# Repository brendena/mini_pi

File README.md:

# MINI_PI

The goal is to make a board that you can use to replace the inside of a mac mini.  

The goal is to use as much of the original as possible.  
* case
* power supply
* wifi antenna 
* heatsink
* fan

Parts
* Mac mini 2013

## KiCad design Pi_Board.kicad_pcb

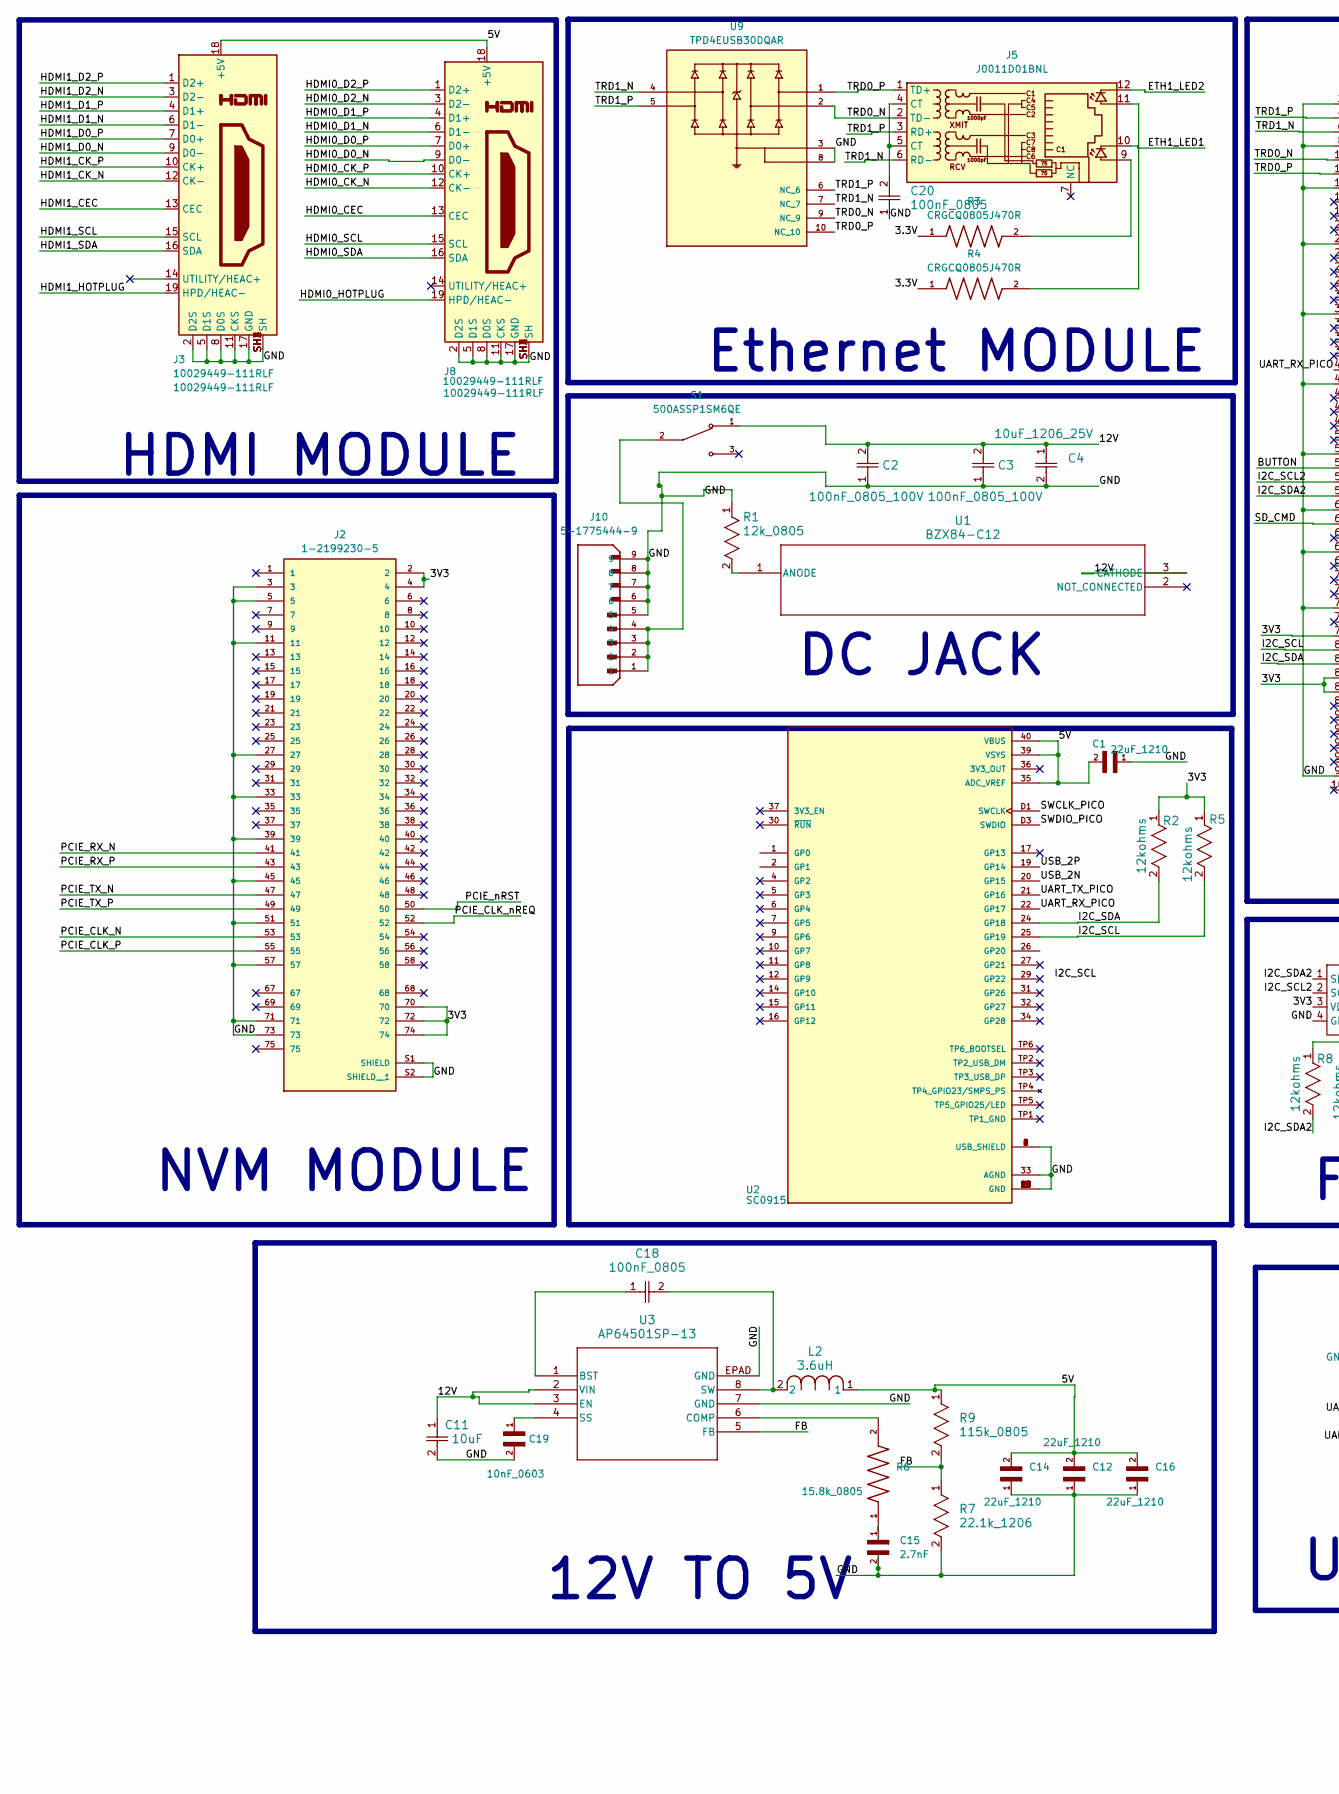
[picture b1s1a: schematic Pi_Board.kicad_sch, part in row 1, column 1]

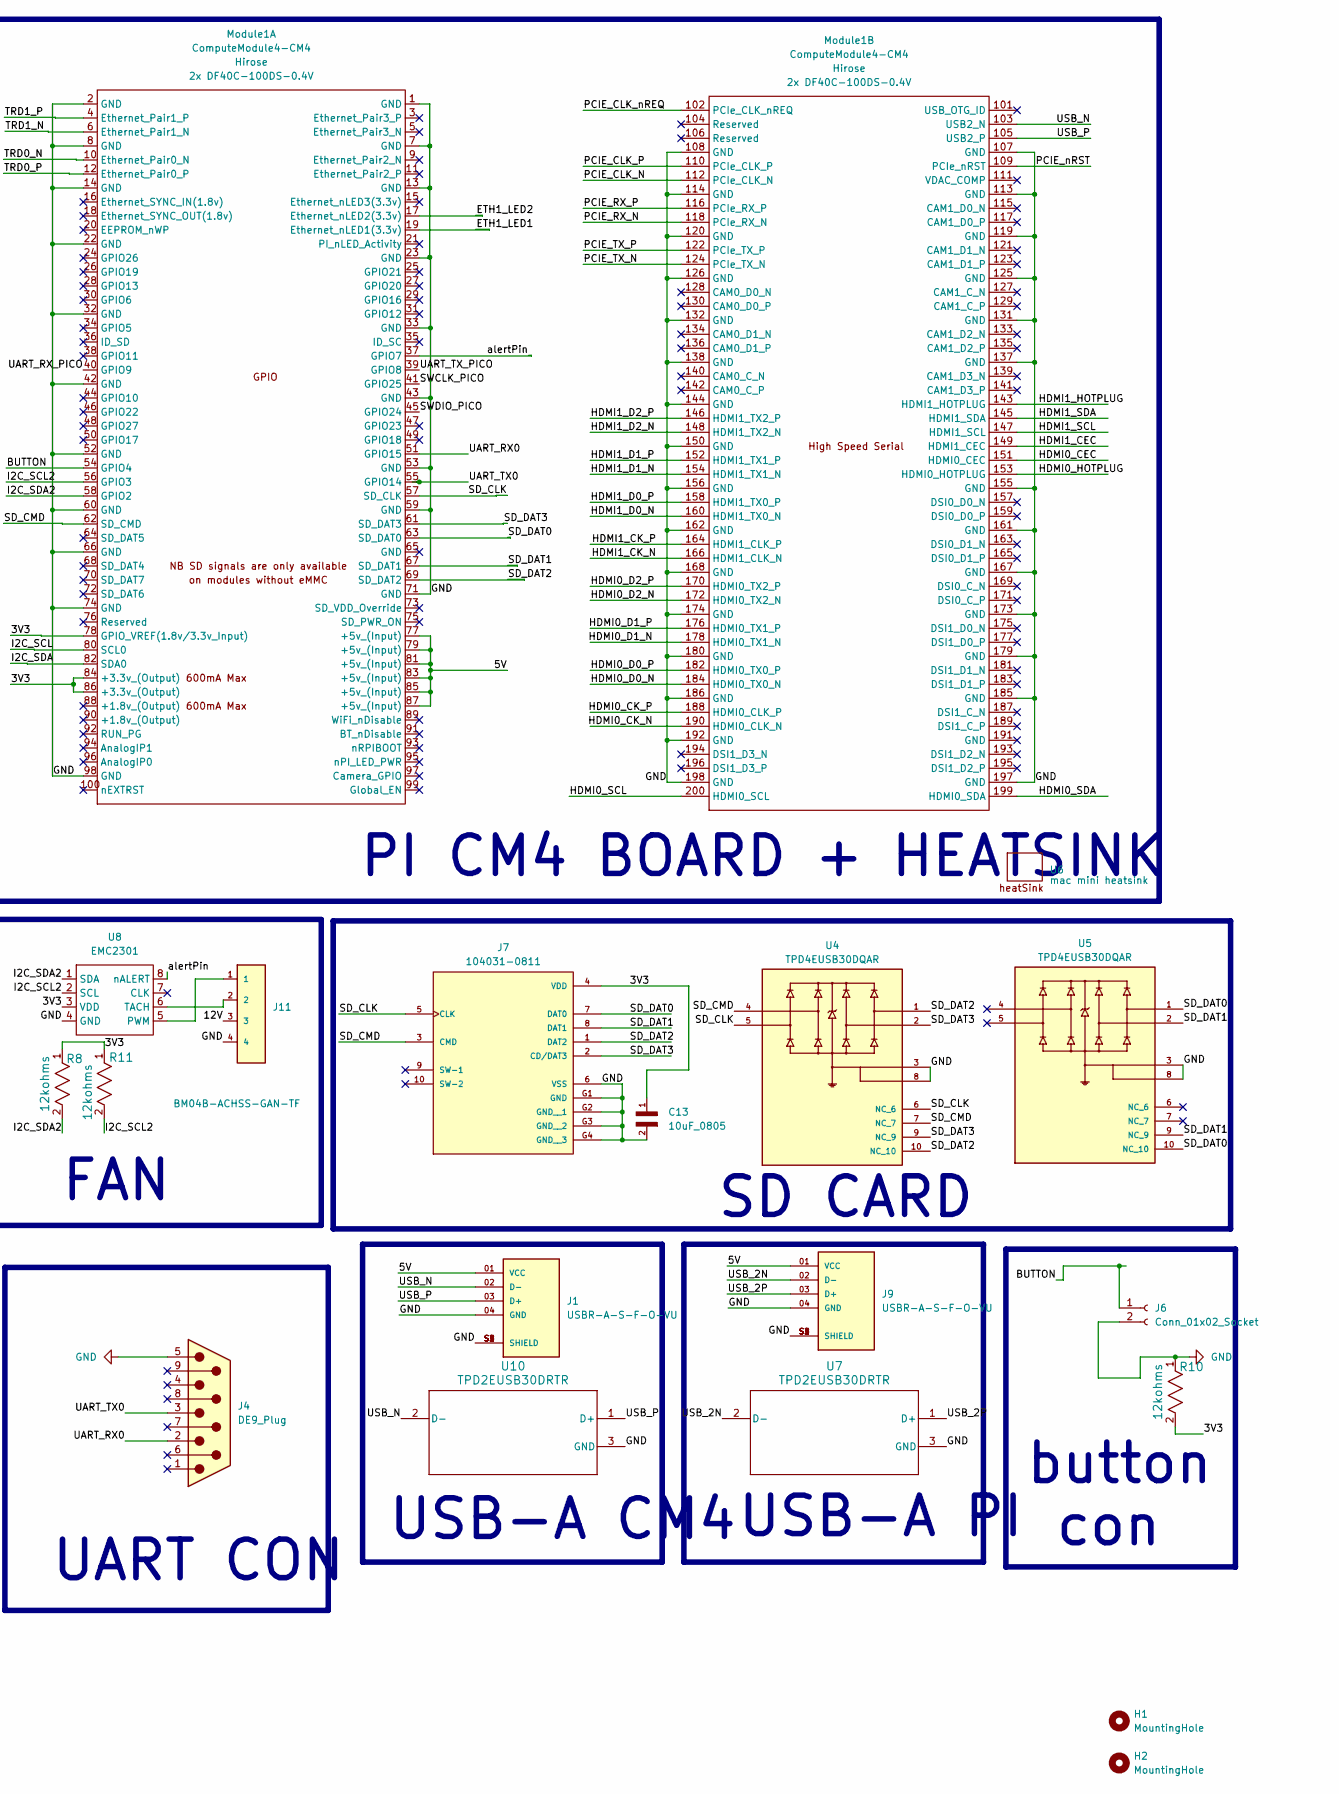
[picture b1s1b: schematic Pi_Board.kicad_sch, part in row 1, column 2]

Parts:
C1, C12, C14, C16: 22uF_1210; CAPC3225X270N
C2, C3: 100nF_0805_100V; RC0805N_YAG
C4: 10uF_1206_25V; CAP_3216_TDK-M
C11: 10uF; CAP_CL31_SAM; Part Number CL31A106MAHNNNE
C13: 10uF_0805; CAPC2012X135N
C15: 2.7nF; CAPC1608X90; Part Number CC0603KRX7R9BB272
C18, C20: 100nF_0805; CAP_CC0805_YAG-L
C19: 10nF_0603; CAPC1608X90
H1, H2: MountingHole; MountingHole_2.2mm_M2_DIN965_Pad
J1, J9: USBR-A-S-F-O-VU; SAMTEC_USBR-A-S-F-O-VU; PARTREV C
J2: 1-2199230-5; TE_1-2199230-5; PARTREV B3
J3, J8: 10029449-111RLF; AMPHENOL_10029449-111RLF; Part Number 10029449-111RLF
J4: DE9_Plug; DSUB-9_Female_Horizontal_P2.77x2.84mm_EdgePinOffset7.70mm_H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
J5: J0011D01BNL; CONN12_011D01BNL_PUL
J6: Conn_01x02_Socket; Molex_KK-254_AE-6410-02A_1x02_P2.54mm_Vertical
J7: 104031-0811; SDCARD_MOLEX_503398-1892; PARTREV B2
J10: 5-1775444-9; TE_5-1775444-9
J11: BM04B-ACHSS-GAN-TF; JST_BM04B-ACHSS-GAN-TF
L2: 3.6uH; L_6.3x6.3_H3; Part Number FNR5040S3R6MT
Module1: ComputeModule4-CM4; Raspberry-Pi-4-Compute-Module
R1: 12k_0805; RES_WR08_WRE-M
R2, R5, R8, R10, R11: 12kohms; RC0402N_YAG; Part Number RC0402FR-0712KL
R3, R4: CRGCQ0805J470R; RESC2012X65N
R6: 15.8k_0805; RESC2012X60N
R7: 22.1k_1206; RC1206N_YAG-L
R9: 115k_0805; RC0805N_YAG-M
S1: 500ASSP1SM6QE; SW_500ASSP1SM6QE; PARTREV A
U1: BZX84-C12; SOT23_NXP-M
U2: SC0915; MODULE_SC0915; PARTREV 1.9
U3: AP64501SP-13; SO-8EP_DIO
U4, U5, U9: TPD4EUSB30DQAR; IC_TPD4EUSB30DQAR; PARTREV F
U6: mac mini heatsink; heatsink
U7, U10: TPD2EUSB30DRTR; DRT0003A
U8: EMC2301; MSOP8_MC_MCH

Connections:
/3.3V: R3.1, R4.1
/3V3: C13.1, J2.2, J2.4, J2.70, J2.72, J2.74, J7.4 (VDD), Module1.78 (GPIO_VREF(1.8v/3.3v_Input)), Module1.84 (+3.3v_(Output)), Module1.86 (+3.3v_(Output)), R2.1, R5.1, R8.1, R10.2, R11.1, U8.3 (VDD)
/5V: C1.2, C12.2, C14.2, C16.2, J1.01 (VCC), J3.18 (+5V), J8.18 (+5V), J9.01 (VCC), L2.1, Module1.77 (+5v_(Input)), Module1.79 (+5v_(Input)), Module1.81 (+5v_(Input)), Module1.83 (+5v_(Input)), Module1.85 (+5v_(Input)), Module1.87 (+5v_(Input)), R9.1, U2.35 (ADC_VREF), U2.39 (VSYS), U2.40 (VBUS)
/12V: C2.2, C3.2, C4.1, C11.1, J11.3, S1.1, U1.3 (CATHODE), U3.2 (VIN), U3.3 (EN)
/BUTTON: J6.1, Module1.54 (GPIO4)
/ETH1_LED1: J5.10, Module1.19 (Ethernet_nLED1(3.3v))
/ETH1_LED2: J5.12, Module1.17 (Ethernet_nLED2(3.3v))
/FB: R7.1, R9.2, U3.5 (FB)
/HDMI0_CEC: J8.13 (CEC), Module1.151 (HDMI0_CEC)
/HDMI0_CK_N: J8.12 (CK-), Module1.190 (HDMI0_CLK_N)
/HDMI0_CK_P: J8.10 (CK+), Module1.188 (HDMI0_CLK_P)
/HDMI0_D0_N: J8.9 (D0-), Module1.184 (HDMI0_TX0_N)
/HDMI0_D0_P: J8.7 (D0+), Module1.182 (HDMI0_TX0_P)
/HDMI0_D1_N: J8.6 (D1-), Module1.178 (HDMI0_TX1_N)
/HDMI0_D1_P: J8.4 (D1+), Module1.176 (HDMI0_TX1_P)
/HDMI0_D2_N: J8.3 (D2-), Module1.172 (HDMI0_TX2_N)
/HDMI0_D2_P: J8.1 (D2+), Module1.170 (HDMI0_TX2_P)
/HDMI0_HOTPLUG: J8.19 (HPD/HEAC-), Module1.153 (HDMI0_HOTPLUG)
/HDMI0_SCL: J8.15 (SCL), Module1.200 (HDMI0_SCL)
/HDMI0_SDA: J8.16 (SDA), Module1.199 (HDMI0_SDA)
/HDMI1_CEC: J3.13 (CEC), Module1.149 (HDMI1_CEC)
/HDMI1_CK_N: J3.12 (CK-), Module1.166 (HDMI1_CLK_N)
/HDMI1_CK_P: J3.10 (CK+), Module1.164 (HDMI1_CLK_P)
/HDMI1_D0_N: J3.9 (D0-), Module1.160 (HDMI1_TX0_N)
/HDMI1_D0_P: J3.7 (D0+), Module1.158 (HDMI1_TX0_P)
/HDMI1_D1_N: J3.6 (D1-), Module1.154 (HDMI1_TX1_N)
/HDMI1_D1_P: J3.4 (D1+), Module1.152 (HDMI1_TX1_P)
/HDMI1_D2_N: J3.3 (D2-), Module1.148 (HDMI1_TX2_N)
/HDMI1_D2_P: J3.1 (D2+), Module1.146 (HDMI1_TX2_P)
/HDMI1_HOTPLUG: J3.19 (HPD/HEAC-), Module1.143 (HDMI1_HOTPLUG)
/HDMI1_SCL: J3.15 (SCL), Module1.147 (HDMI1_SCL)
/HDMI1_SDA: J3.16 (SDA), Module1.145 (HDMI1_SDA)
/I2C_SCL: Module1.80 (SCL0), R5.2, U2.25 (GP19)
/I2C_SCL2: Module1.56 (GPIO3), R11.2, U8.2 (SCL)
/I2C_SDA: Module1.82 (SDA0), R2.2, U2.24 (GP18)
/I2C_SDA2: Module1.58 (GPIO2), R8.2, U8.1 (SDA)
/PCIE_CLK_N: J2.53, Module1.112 (PCIe_CLK_N)
/PCIE_CLK_P: J2.55, Module1.110 (PCIe_CLK_P)
/PCIE_CLK_nREQ: J2.52, Module1.102 (PCIe_CLK_nREQ)
/PCIE_RX_N: J2.41, Module1.118 (PCIe_RX_N)
/PCIE_RX_P: J2.43, Module1.116 (PCIe_RX_P)
/PCIE_TX_N: J2.47, Module1.124 (PCIe_TX_N)
/PCIE_TX_P: J2.49, Module1.122 (PCIe_TX_P)
/PCIE_nRST: J2.50, Module1.109 (PCIe_nRST)
/SD_CLK: J7.5 (CLK), Module1.57 (SD_CLK), U4.5, U4.6 (NC)
/SD_CMD: J7.3 (CMD), Module1.62 (SD_CMD), U4.4, U4.7 (NC)
/SD_DAT0: J7.7 (DAT0), Module1.63 (SD_DAT0), U5.1, U5.10 (NC)
/SD_DAT1: J7.8 (DAT1), Module1.67 (SD_DAT1), U5.2, U5.9 (NC)
/SD_DAT2: J7.1 (DAT2), Module1.69 (SD_DAT2), U4.1, U4.10 (NC)
/SD_DAT3: J7.2 (CD/DAT3), Module1.61 (SD_DAT3), U4.2, U4.9 (NC)
/SWCLK_PICO: Module1.41 (GPIO25), U2.D1 (SWCLK)
/SWDIO_PICO: Module1.45 (GPIO24), U2.D3 (SWDIO)
/TRD0_N: J5.2 (TD-), Module1.10 (Ethernet_Pair0_N), U9.2, U9.9 (NC)
/TRD0_P: J5.1 (TD+), Module1.12 (Ethernet_Pair0_P), U9.1, U9.10 (NC)
/TRD1_N: J5.6 (RD-), Module1.6 (Ethernet_Pair1_N), U9.4, U9.7 (NC)
/TRD1_P: J5.3 (RD+), Module1.4 (Ethernet_Pair1_P), U9.5, U9.6 (NC)
/UART_RX0: J4.2, Module1.51 (GPIO15)
/UART_RX_PICO: Module1.40 (GPIO9), U2.22 (GP17)
/UART_TX0: J4.3, Module1.55 (GPIO14)
/UART_TX_PICO: Module1.39 (GPIO8), U2.21 (GP16)
/USB_2N: J9.02 (D-), U2.20 (GP15), U7.2 (D-)
/USB_2P: J9.03 (D+), U2.19 (GP14), U7.1 (D+)
/USB_N: J1.02 (D-), Module1.103 (USB2_N), U10.2 (D-)
/USB_P: J1.03 (D+), Module1.105 (USB2_P), U10.1 (D+)
/alertPin: Module1.37 (GPIO7), U8.8 (nALERT)
GND: C1.1, C2.1, C3.1, C4.2, C11.2, C12.1, C13.2, C14.1, C15.2, C16.1, C19.2, C20.1, J1.04 (GND), J1.S1 (SHIELD), J1.S2 (SHIELD), J1.S3 (SHIELD), J1.S4 (SHIELD), J2.3, J2.5, J2.11, J2.27, J2.33, J2.39, J2.45, J2.51, J2.57, J2.71, J2.73, J2.S1 (SHIELD), J2.S2 (SHIELD__1), J3.2 (D2S), J3.5 (D1S), J3.8 (D0S), J3.11 (CKS), J3.17 (GND), J3.SH1 (SH), J3.SH2 (SH), J3.SH3 (SH), J3.SH4 (SH), J4.5, J6.2, J7.6 (VSS), J7.G1 (GND), J7.G2 (GND__1), J7.G3 (GND__2), J7.G4 (GND__3), J8.2 (D2S), J8.5 (D1S), J8.8 (D0S), J8.11 (CKS), J8.17 (GND), J8.SH1 (SH), J8.SH2 (SH), J8.SH3 (SH), J8.SH4 (SH), J9.04 (GND), J9.S1 (SHIELD), J9.S2 (SHIELD), J9.S3 (SHIELD), J9.S4 (SHIELD), J10.5, J10.6, J10.7, J10.8, J10.9, J11.4, Module1.1 (GND), Module1.2 (GND), Module1.7 (GND), Module1.8 (GND), Module1.13 (GND), Module1.14 (GND), Module1.22 (GND), Module1.23 (GND), Module1.32 (GND), Module1.33 (GND), Module1.42 (GND), Module1.43 (GND), Module1.52 (GND), Module1.53 (GND), Module1.59 (GND), Module1.60 (GND), Module1.66 (GND), Module1.71 (GND), Module1.74 (GND), Module1.98 (GND), Module1.107 (GND), Module1.108 (GND), Module1.113 (GND), Module1.114 (GND), Module1.119 (GND), Module1.120 (GND), Module1.125 (GND), Module1.126 (GND), Module1.131 (GND), Module1.132 (GND), Module1.137 (GND), Module1.138 (GND), Module1.144 (GND), Module1.150 (GND), Module1.155 (GND), Module1.156 (GND), Module1.161 (GND), Module1.162 (GND), Module1.167 (GND), Module1.168 (GND), Module1.173 (GND), Module1.174 (GND), Module1.179 (GND), Module1.180 (GND), Module1.185 (GND), Module1.186 (GND), Module1.192 (GND), Module1.197 (GND), Module1.198 (GND), R1.1, R7.2, R10.1, U2.3 (GND), U2.8 (GND), U2.13 (GND), U2.18 (GND), U2.23 (GND), U2.28 (GND), U2.33 (AGND), U2.38 (GND), U2.A (USB_SHIELD), U2.B (USB_SHIELD), U2.C (USB_SHIELD), U2.D (USB_SHIELD), U2.D2 (GND), U3.7 (GND), U3.EPAD (GND), U4.3, U4.8, U5.3, U5.8, U7.3 (GND), U8.4 (GND), U9.3, U9.8, U10.3 (GND)
unnamed: C15.1, R6.1
unnamed: C20.2, J5.4 (CT), J5.5 (CT)
unnamed: J5.9, R3.2
unnamed: J5.11, R4.2
unnamed: J10.1, J10.2, J10.3, J10.4, S1.2
unnamed: R1.2, U1.1 (ANODE)
unnamed: C18.1, U3.1 (BST)
unnamed: R6.2, U3.6 (COMP)
unnamed: C19.1, U3.4 (SS)
unnamed: C18.2, L2.2, U3.8 (SW)
unnamed: J11.1, U8.5 (PWM)
unnamed: J11.2, U8.6 (TACH)

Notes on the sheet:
HDMI MODULE
SD CARD
DC JACK
UART CON
PI CM4 BOARD + HEATSINK
12V TO 5V
Ethernet MODULE
NVM MODULE
FAN
button con
USB-A CM4
USB-A PI

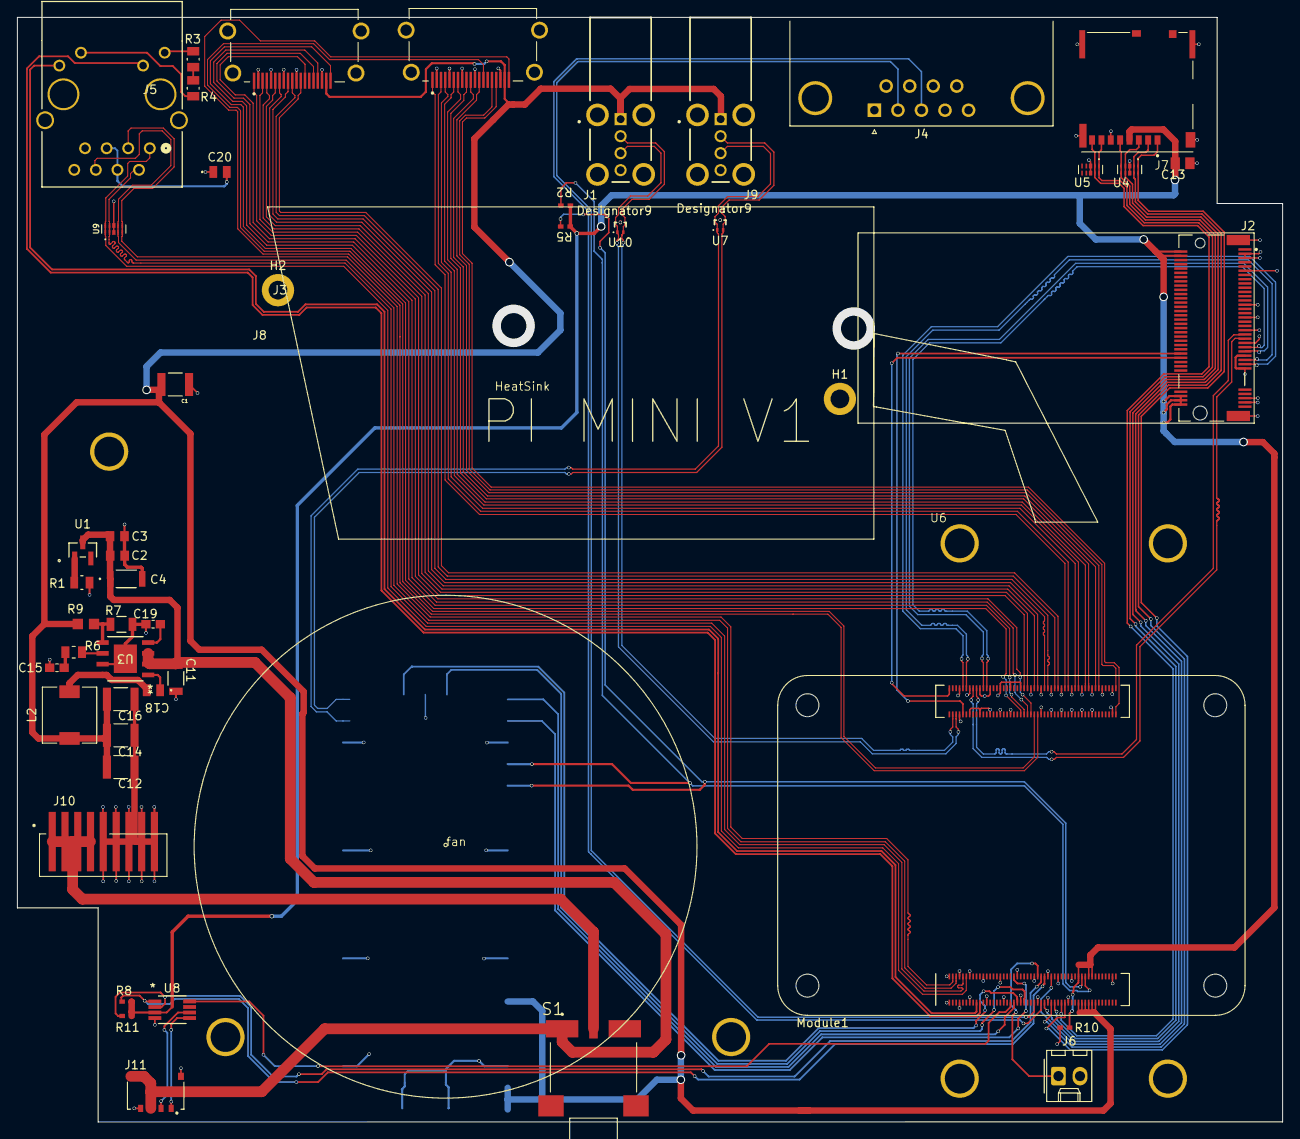
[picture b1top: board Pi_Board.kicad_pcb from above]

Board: 4 copper layers, 148.9 x 130.0 mm, 50 parts (1 on the bottom side), 78 nets.

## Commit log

2024-07-27 ready to send out
2024-08-10 pushed V1
2024-08-10 compress the V1 into a file
